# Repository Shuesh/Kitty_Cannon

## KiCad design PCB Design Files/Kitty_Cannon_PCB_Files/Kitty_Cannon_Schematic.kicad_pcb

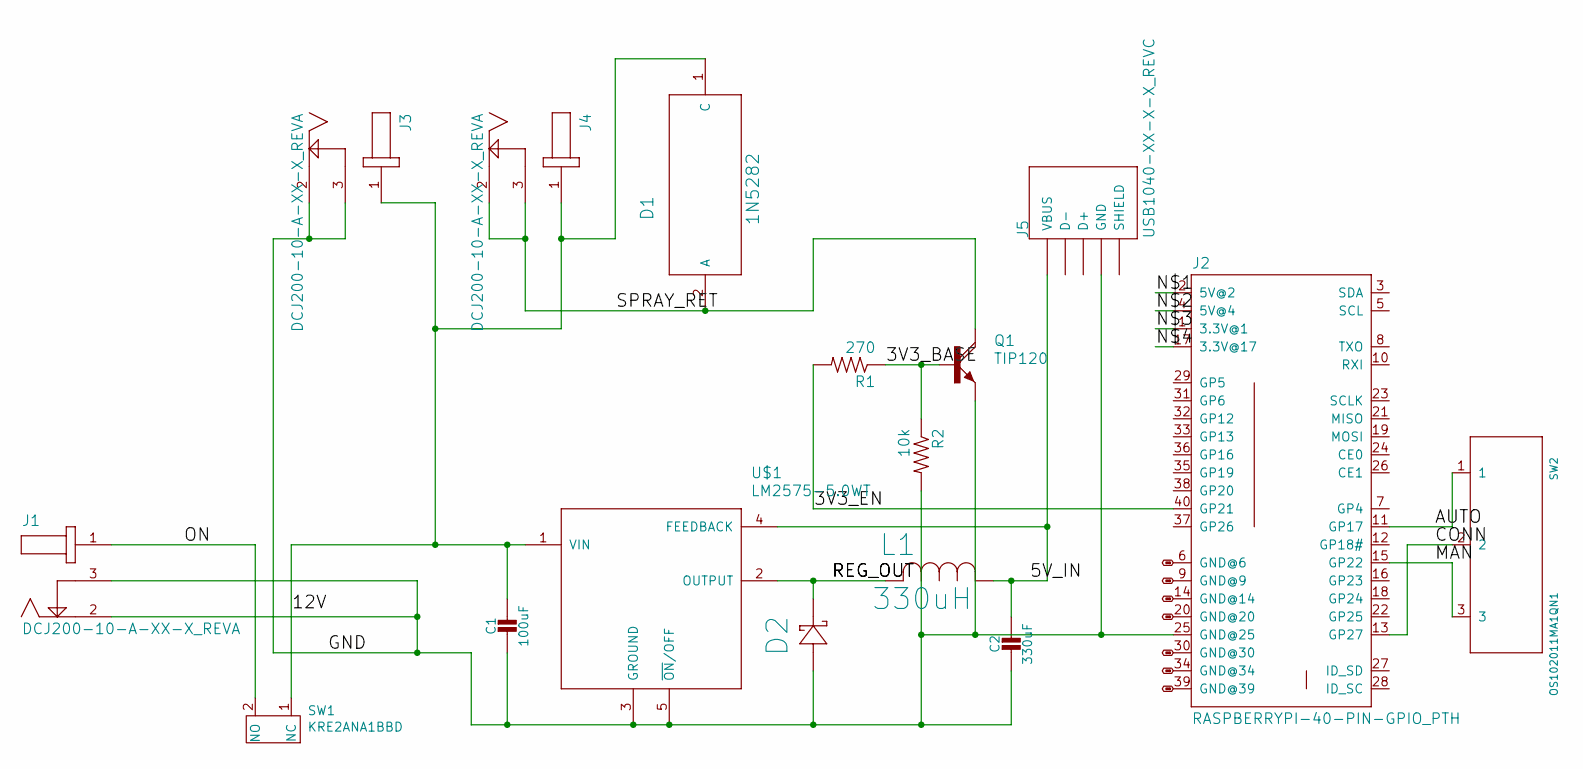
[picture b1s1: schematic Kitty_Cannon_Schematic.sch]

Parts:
C1: 100uF; 860010372006_100UF
C2: 330uF; 860010372006_100UF
D1: 1N5282; DIO_1N5282
D2: SB3100E-G; SB2E-G
J1, J3, J4: DCJ200-10-A-XX-X_REVA; GCT_DCJ200-10-A-XX-X_REVA
J2: RASPBERRYPI-40-PIN-GPIO_PTH; 2X20_SHROUDED
J5: USB1040-XX-X-X_REVC; GCT_USB1040-XX-X-X_REVC
L1: 330uH; 1433428C_MUR
Q1: TIP120; TO220AH
R1: 270; 0204_5
R2: 10k; 0204_5
SW1: KRE2ANA1BBD
SW2: OS102011MA1QN1
U$1: LM2575-5.0WT

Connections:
/3V3_BASE: Q1.B, R1.1, R2.1
/3V3_EN: J2.40 (GP21), R1.2
/5V_IN: C2.1, J5.1 (VBUS), L1.1, U$1.4 (FEEDBACK)
/12V: C1.1, D1.1 (C), J3.1, J4.1, SW1.1 (NC), U$1.1 (VIN)
/AUTO: J2.11 (GP17), SW2.1
/CONN: J2.13 (GP27), SW2.2
/MAN: J2.15 (GP22), SW2.3
/N$1: J2.2 (5V@2)
/N$2: J2.4 (5V@4)
/N$3: J2.1 (3.3V@1)
/N$4: J2.17 (3.3V@17)
/ON: J1.1, SW1.2 (NO)
/REG_OUT: D2.1, L1.2, U$1.2 (OUTPUT)
/SPRAY_RET: D1.2 (A), J4.2, J4.3, Q1.C
GND: C1.2, C2.2, D2.2, J1.2, J1.3, J2.6 (GND@6), J2.9 (GND@9), J2.14 (GND@14), J2.20 (GND@20), J2.25 (GND@25), J2.30 (GND@30), J2.34 (GND@34), J2.39 (GND@39), J3.2, J3.3, J5.4 (GND), Q1.E, R2.2, U$1.3 (GROUND), U$1.5 (~ON~/OFF)
unnamed: J5.5 (SHIELD), J5.6 (SHIELD)

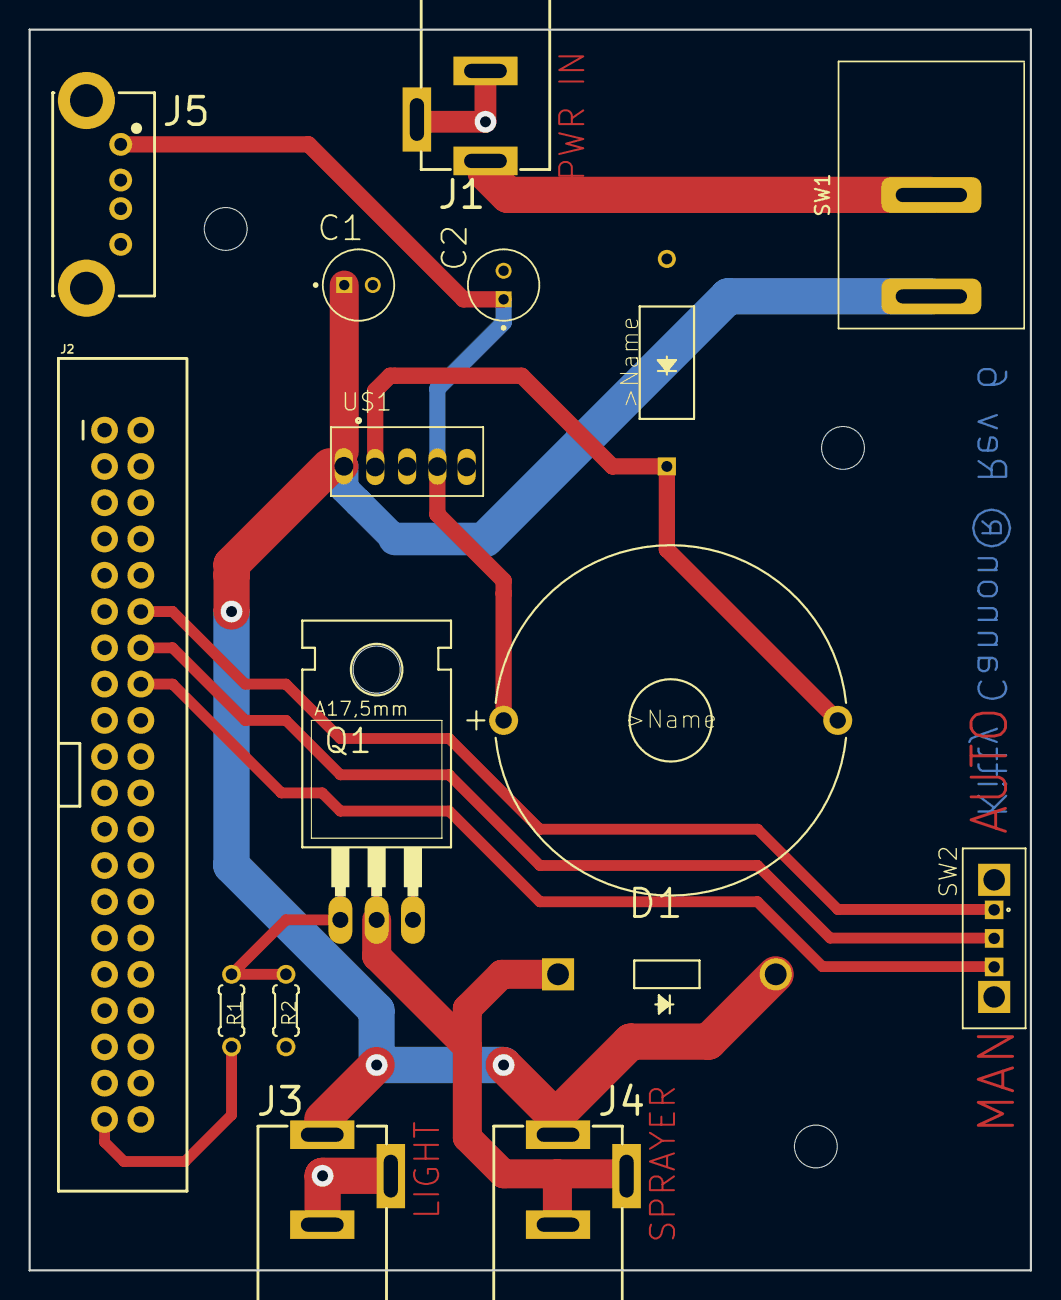
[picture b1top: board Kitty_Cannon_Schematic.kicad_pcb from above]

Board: 2 copper layers, 70.1 x 86.9 mm, 16 parts (0 on the bottom side), 12 nets.

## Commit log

2021-02-18 Main creation
2021-02-18 Adding requirements.txt
2021-02-18 added import opencv
2021-02-18 Main skeleton
2021-02-18 Adding config
2021-05-15 servo pwm, changes to requirements, added to init
2021-07-13 Add component notes
2021-08-14 More polished GUI and some work done on Main.py
2021-08-28 Polished interface, just started implementing JavaScript.
2021-08-28 Additional Files
2021-09-28 Eagle Project Files
2021-12-05 Kitty Cannon - update structure
2021-12-05 remove rdp file
2021-12-05 Reorganizing
2022-03-21 Update to track cat faces and not humans
2022-07-22 Updated html, added svgs and refactored css
2022-07-22 Transition to flask framework as it's running on rpi
2022-07-22 update to script.js position and link in html
2022-07-22 alter js location
2022-07-22 reposition js
2022-07-23 Edit to use AJAX for passing button commands to Flask
2022-07-23 Tried rearranging some things
2022-07-23 Working Flask and JS connection
2022-07-23 Minor changes to camera.py
2022-07-23 Beginning image processing and manual control. Reorganized haar cascades
2022-07-26 Working gpio_interface and manual modules
2022-07-26 Frontend to servo positioning pipeline complete - Manual

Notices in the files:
parts and their libraries:
SparkFun-Connectors: Licensing: Creative Commons ShareAlike 4.0 International - https://creativecommons.org/licenses/by-sa/4.0
SB3100E-G_Schottky: COPYRIGHT: Copyright (C) 2021 Ultra Librarian. All rights reserved.
